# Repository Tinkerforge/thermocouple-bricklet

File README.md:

# thermocouple-bricklet
 Reads temperatures from thermocouples

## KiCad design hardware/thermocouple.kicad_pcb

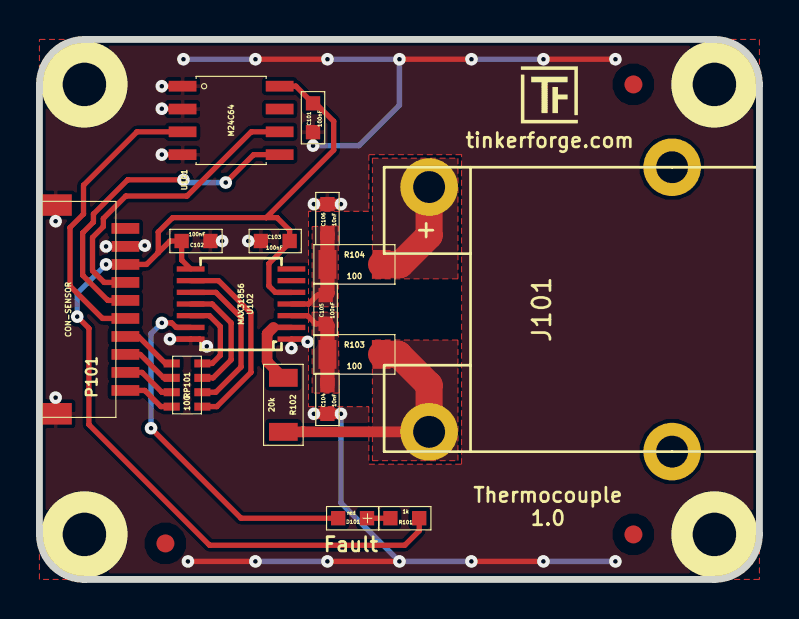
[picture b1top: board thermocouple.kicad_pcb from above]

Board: 2 copper layers, 40.0 x 30.0 mm, 24 parts (0 on the bottom side), 20 nets.

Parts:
C101, C102, C103, C105: 100nF; 0603
C104, C106: 10nF; 0603
D101: red; D0603
Fiducial_Mark: VAL**; Fiducial_Mark
Fiducial_Mark#2, Fiducial_Mark#3: VAL**; Fiducial_Mark
J101: THERM; PCC_SMP
P101: CON-SENSOR
R101: 1k; 0603
R102: 20k; 1206
R103, R104: 100; 1206
RP101: 100; 0603X4
U101: M24C64; SOIC8
U102: MAX31856; TSSOP14
U103, U104, U105, U106: DRILL; DRILL_NP
VAL: CE_5mm

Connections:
GND: C101.2, C102.2, C103.2, C104.2, C106.1, P101.2, P101.EP, U101.1, U101.2, U101.4, U102.1, U102.14
unnamed: C104.1, C105.2, R103.2, U102.3
unnamed: C105.1, C106.2, R104.2, U102.4
unnamed: D101.1, R101.1
unnamed: D101.2, U102.13
unnamed: J101.1, R104.1
unnamed: J101.2, R102.1, R103.1
unnamed: P101.4, U101.6
unnamed: P101.5, U101.5
unnamed: P101.6, U101.3
unnamed: P101.7, RP101.5
unnamed: P101.8, RP101.6
unnamed: P101.9, RP101.7
unnamed: P101.10, RP101.8
unnamed: R102.2, U102.2
unnamed: RP101.1, U102.9
unnamed: RP101.2, U102.10
unnamed: RP101.3, U102.11
unnamed: RP101.4, U102.12
VCC: C101.1, C102.1, C103.1, P101.3, R101.2, U101.8, U102.5, U102.8

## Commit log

2015-07-30 initial checkin of thermocouple bricklet prototype
2015-07-30 add fiducials to pcb
2015-07-30 fit size to 5mm grid
2015-07-30 Add readme
2015-08-12 add polarity description
2015-08-13 change terminal block to thermocouple connector
2015-08-27 Add initial impl. for Thermocouple Bricklet
2015-08-27 Add most of the examples
2015-09-01 Fix typo
2015-09-09 Duplicate cmake call to fix bug during cmake creation
2015-09-16 Add JavaScript, MATLAB/Octave and Shell examples
2015-09-30 Generator based example cleanup
2015-10-20 drc check
2015-11-12 matlab: Fix callback handling for R2014a
    http://undocumentedmatlab.com/blog/matlab-callbacks-for-java-events-in-r2014a
2015-11-25 Include date and commit into changelog
2015-11-30 vbnet: Break long line
2016-01-04 Fix version numbers
2016-01-04 Add LabVIEW examples
2016-01-05 Mask open uv/ov fault register for red LED
2016-01-06 Check for all possible averaging values
    Before it was possible to set a non-existing averaging value
2016-01-06 add schematic pdf
2016-01-07 Remove WIP marker
2016-01-11 Update changelog
2016-01-11 Add .gitignore
2016-02-16 Fix signed 19 to signed 32 bit conversion
2016-02-16 Add changelog for firmware version 2.0.1
2016-02-16 Add changelog commit after the fact
2016-05-18 c: Add missing device destroy call
2016-06-29 Whitespace
2016-07-01 Make the change UID comment more explicit
2016-09-02 rename thermocouple connector
2016-11-04 fix npth of thermocouple connector
2017-04-13 csharp: Adapt example
2017-04-21 shell: Adapt example
2017-06-02 octave: Use javaObject instead of deprecated java_new
2017-11-30 Update examples from generator
2017-12-07 mathematica: Also generate .nb files
2018-01-02 change capacitor value
2018-02-02 Update examples
2018-02-19 javascript: Close div tag correctly
2018-02-20 Cleanup KiCad libraries config
    Ensure LibDir=kicad-libraries and LibName1=tinkerforge.
    Remove special library.
2018-05-24 perl: Use strict in examples
2018-07-11 Add Makefile with docker support
2018-07-11 Update directory structure and build instructions
2018-07-11 Remove obsolete generate_makefile scripts
2018-11-06 Add rust examples
2018-11-07 rust: Accept host names for ip connection, fix naming inconsistencies
2018-11-07 rust: Rename callback receivers.
2018-12-14 Add go examples.
2018-12-14 go: Fix printf parameters.
2018-12-18 go: Change import path.
2018-12-18 go: Change import path again.
2018-12-20 rust: Reformat examples.
2019-01-24 mqtt: Add examples.
2019-01-24 mqtt: Fix example header.
2019-01-24 mqtt: Remove executable bit in example permissions.
2019-01-24 go: Minor example fixes.
2019-01-24 mqtt: Minor example fixes.
2019-03-28 mqtt: Fix whitespace.
2019-08-22 c: Adapt to bindings changes
2020-01-13 examples: Use python3 input instead of python2 raw_input.
2020-01-13 examples: mqtt: Remove trailing whitespace.
2021-10-25 Update KiCad link
    https://www.kicad.org/blog/2021/10/Avoid-links-to-former-kicad-domain/
2022-07-06 Add license files.

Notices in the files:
hardware/thermocouple.kicad_pcb:
Licensed under CERN OHL v.1.1
Copyright (©) 2015, B.Nordmeyer
Copyright Tinkerforge GmbH 2015.
This documentation describes Open Hardware and is licensed under the
CERN OHL v. 1.1.
